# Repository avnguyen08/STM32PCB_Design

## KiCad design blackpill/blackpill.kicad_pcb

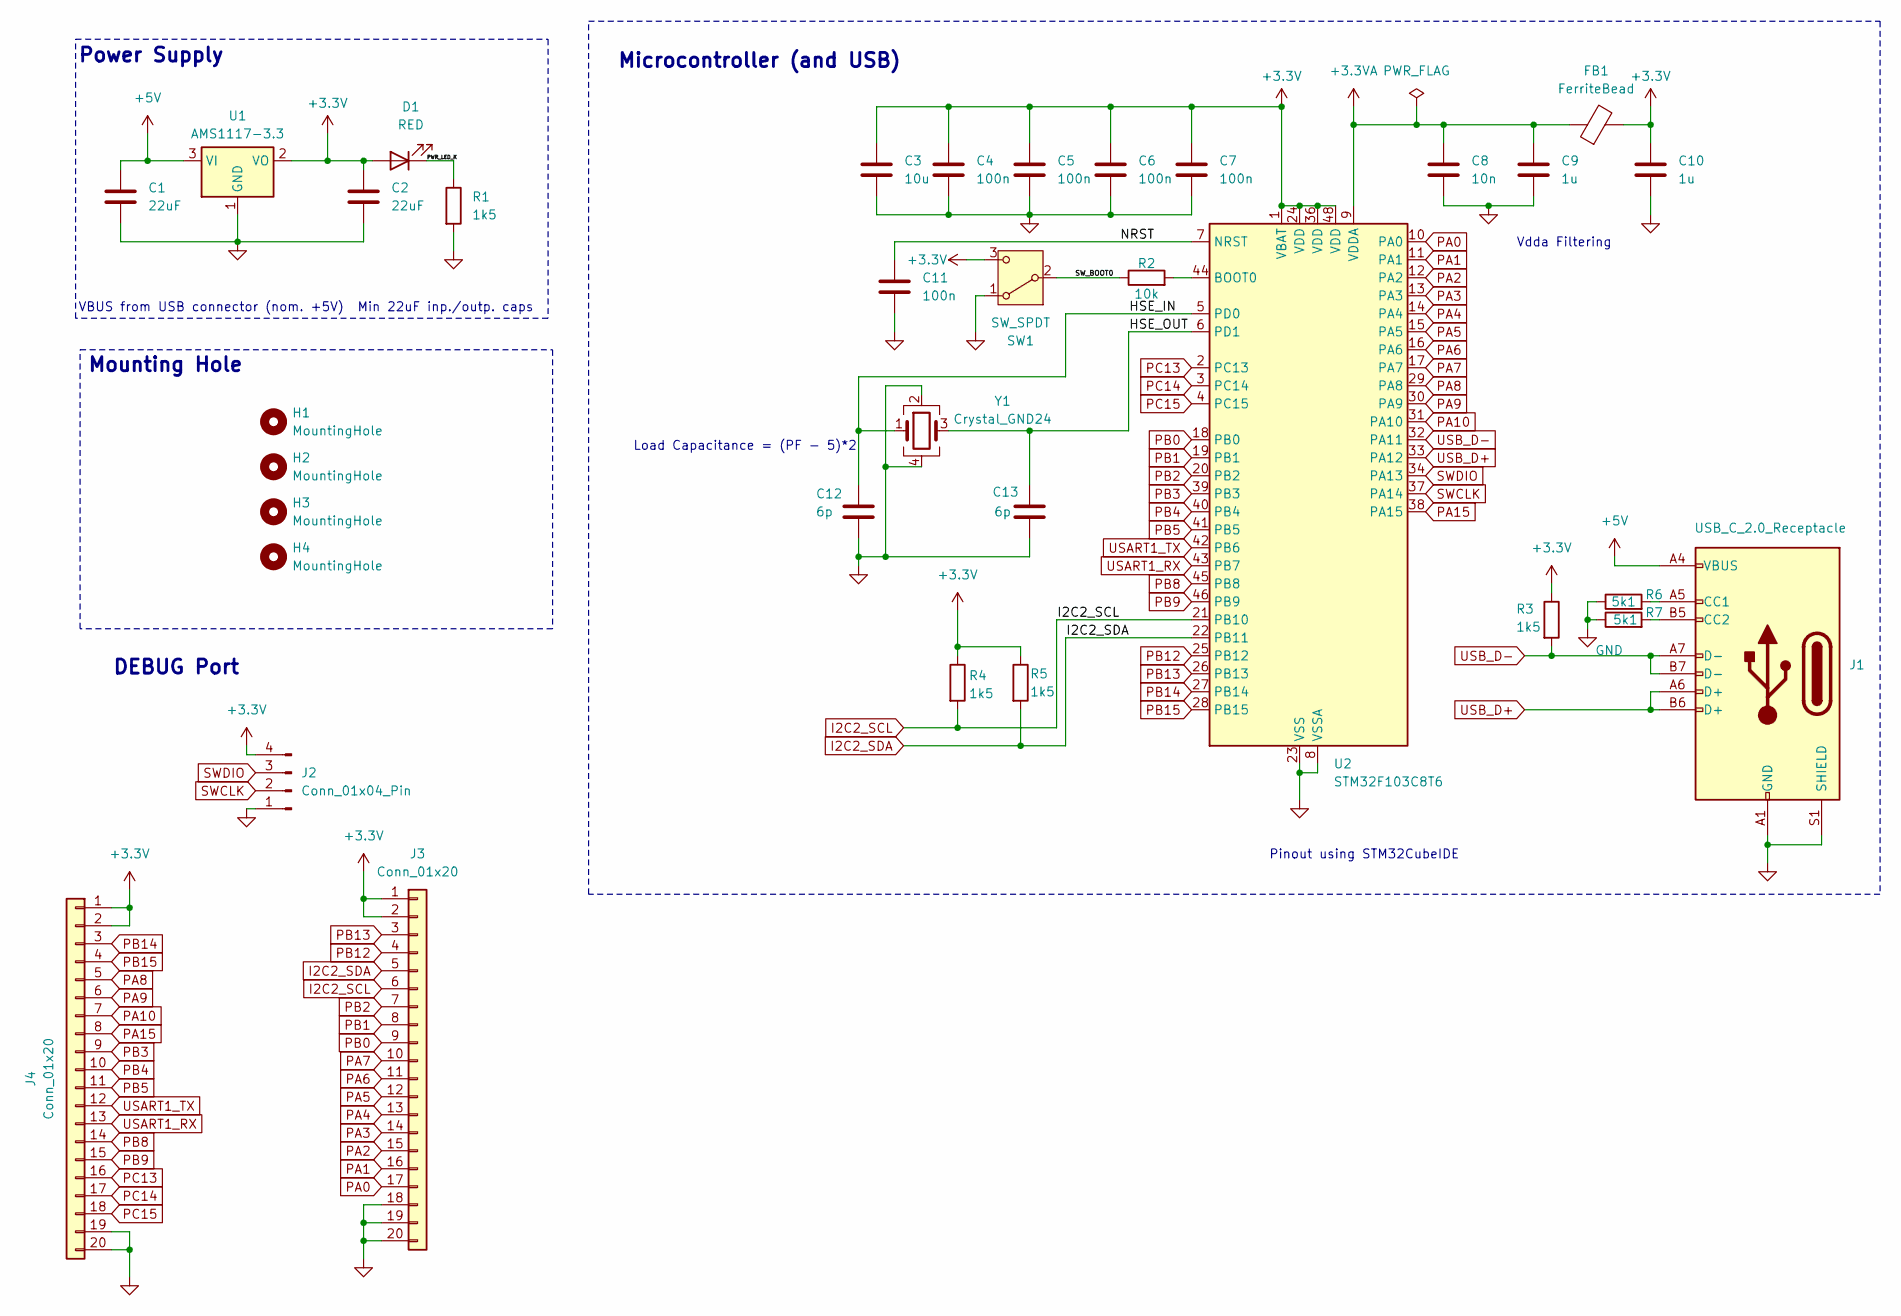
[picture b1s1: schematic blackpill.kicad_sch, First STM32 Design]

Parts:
C1, C2: 22uF; C_0805_2012Metric
C3: 10u; C_0603_1608Metric
C4, C5, C6, C7, C11: 100n; C_0402_1005Metric
C8: 10n; C_0402_1005Metric
C9, C10: 1u; C_0402_1005Metric
C12, C13: 6p; C_0402_1005Metric
D1: RED; LED_0603_1608Metric
FB1: FerriteBead; L_0603_1608Metric
H1, H2, H3, H4: MountingHole; MountingHole_2.2mm_M2
J1: USB_C_2.0_Receptacle; USB_C_Receptacle_GCT_USB4105-xx-A_16P_TopMnt_Horizontal
J2: Conn_01x04_Pin; PinHeader_1x04_P2.54mm_Vertical
J3, J4: Conn_01x20; PinHeader_1x20_P2.54mm_Vertical
R1, R3, R4, R5: 1k5; R_0402_1005Metric
R2: 10k; R_0402_1005Metric
R6, R7: 5k1; R_0402_1005Metric
SW1: SW_SPDT; SW_SPDT_PCM12
U1: AMS1117-3.3; SOT-223-3_TabPin2
U2: STM32F103C8T6; LQFP-48_7x7mm_P0.5mm
Y1: Crystal_GND24; Crystal_SMD_3225-4Pin_3.2x2.5mm_HandSoldering

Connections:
+3.3V: C2.1, C3.1, C4.1, C5.1, C6.1, C7.1, C10.1, D1.2 (A), FB1.2, J2.4, J3.1, J3.2, J4.1, J4.2, R3.1, R4.1, R5.1, SW1.3 (C), U1.2 (VO), U2.1 (VBAT), U2.24 (VDD), U2.36 (VDD), U2.48 (VDD)
+3.3VA: C8.1, C9.1, FB1.1, U2.9 (VDDA)
+5V: C1.1, J1.A4 (VBUS), J1.A9 (VBUS), J1.B4 (VBUS), J1.B9 (VBUS), U1.3 (VI)
/HSE_IN: C12.1, U2.5 (PD0), Y1.1
/HSE_OUT: C13.1, U2.6 (PD1), Y1.3
/NRST: C11.1, U2.7 (NRST)
/PWR_LED_K: D1.1 (K), R1.1
/SW_BOOT0: R2.1, SW1.2 (B)
GND: C1.2, C2.2, C3.2, C4.2, C5.2, C6.2, C7.2, C8.2, C9.2, C10.2, C11.2, C12.2, C13.2, J1.A1 (GND), J1.A12 (GND), J1.B1 (GND), J1.B12 (GND), J1.S1 (SHIELD), J2.1, J3.18, J3.19, J3.20, J4.19, J4.20, R1.2, R6.1, R7.1, SW1.1 (A), U1.1 (GND), U2.8 (VSSA), U2.23 (VSS), U2.35 (VSS), U2.47 (VSS), Y1.2, Y1.4
I2C2_SCL: J3.6, R4.2, U2.21 (PB10)
I2C2_SDA: J3.5, R5.2, U2.22 (PB11)
unnamed: J1.A5 (CC1), R6.2
unnamed: J1.B5 (CC2), R7.2
unnamed: R2.2, U2.44 (BOOT0)
PA0: J3.17, U2.10 (PA0)
PA1: J3.16, U2.11 (PA1)
PA2: J3.15, U2.12 (PA2)
PA3: J3.14, U2.13 (PA3)
PA4: J3.13, U2.14 (PA4)
PA5: J3.12, U2.15 (PA5)
PA6: J3.11, U2.16 (PA6)
PA7: J3.10, U2.17 (PA7)
PA8: J4.5, U2.29 (PA8)
PA9: J4.6, U2.30 (PA9)
PA10: J4.7, U2.31 (PA10)
PA15: J4.8, U2.38 (PA15)
PB0: J3.9, U2.18 (PB0)
PB1: J3.8, U2.19 (PB1)
PB2: J3.7, U2.20 (PB2)
PB3: J4.9, U2.39 (PB3)
PB4: J4.10, U2.40 (PB4)
PB5: J4.11, U2.41 (PB5)
PB8: J4.14, U2.45 (PB8)
PB9: J4.15, U2.46 (PB9)
PB12: J3.4, U2.25 (PB12)
PB13: J3.3, U2.26 (PB13)
PB14: J4.3, U2.27 (PB14)
PB15: J4.4, U2.28 (PB15)
PC13: J4.16, U2.2 (PC13)
PC14: J4.17, U2.3 (PC14)
PC15: J4.18, U2.4 (PC15)
SWCLK: J2.2, U2.37 (PA14)
SWDIO: J2.3, U2.34 (PA13)
USART1_RX: J4.13, U2.43 (PB7)
USART1_TX: J4.12, U2.42 (PB6)
USB_D+: J1.A6 (D+), J1.B6 (D+), U2.33 (PA12)
USB_D-: J1.A7 (D-), J1.B7 (D-), R3.2, U2.32 (PA11)

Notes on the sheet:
Mounting Hole
Load Capacitance = (PF - 5)*2
Microcontroller (and USB)
DEBUG Port
Vdda Filtering
Power Supply
VBUS from USB connector (nom. +5V) Min 22uF inp./outp. caps
Pinout using STM32CubeIDE

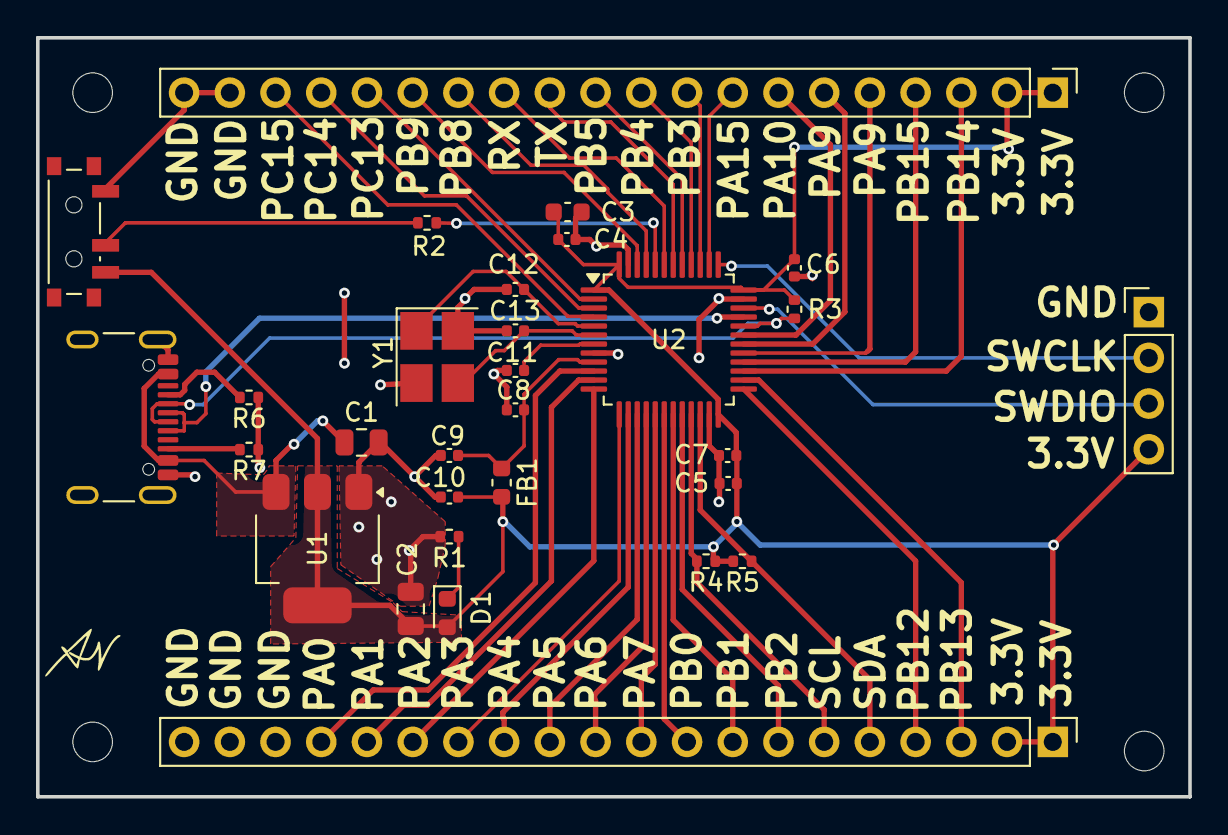
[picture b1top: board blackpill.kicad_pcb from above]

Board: 2 copper layers, 64.0 x 42.2 mm, 34 parts (0 on the bottom side), 47 nets.

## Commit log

2024-03-15 first design
